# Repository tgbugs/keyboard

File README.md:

# kicad libs and mods needed
https://github.com/tmk/kicad_lib_tmk.git
https://github.com/tmk/keyboard_parts.pretty
https://github.com/stormbard/Keyboard.pretty.git
https://github.com/XenGi/kicad_teensy.git
# use this guide
https://github.com/ruiqimao/keyboard-pcb-guide
# keyboard layout editor
https://github.com/swill/kb_builder
http://www.keyboard-layout-editor.com
# teensy setup on gentoo
Need dev-embedded/teensyduino and dev-embedded/teensy_loader_cli, working ebuilds in https://github.com/tgbugs/tgbugs-overlay.
# freerout is basically a necisity use this repo
https://github.com/nick-less/freerouting
Some setup needed to get maven to play nice. Just read the errors.
# gerbv
Before shipping out the gerber files do a once over in something other than kicad. `emerge gerbv`

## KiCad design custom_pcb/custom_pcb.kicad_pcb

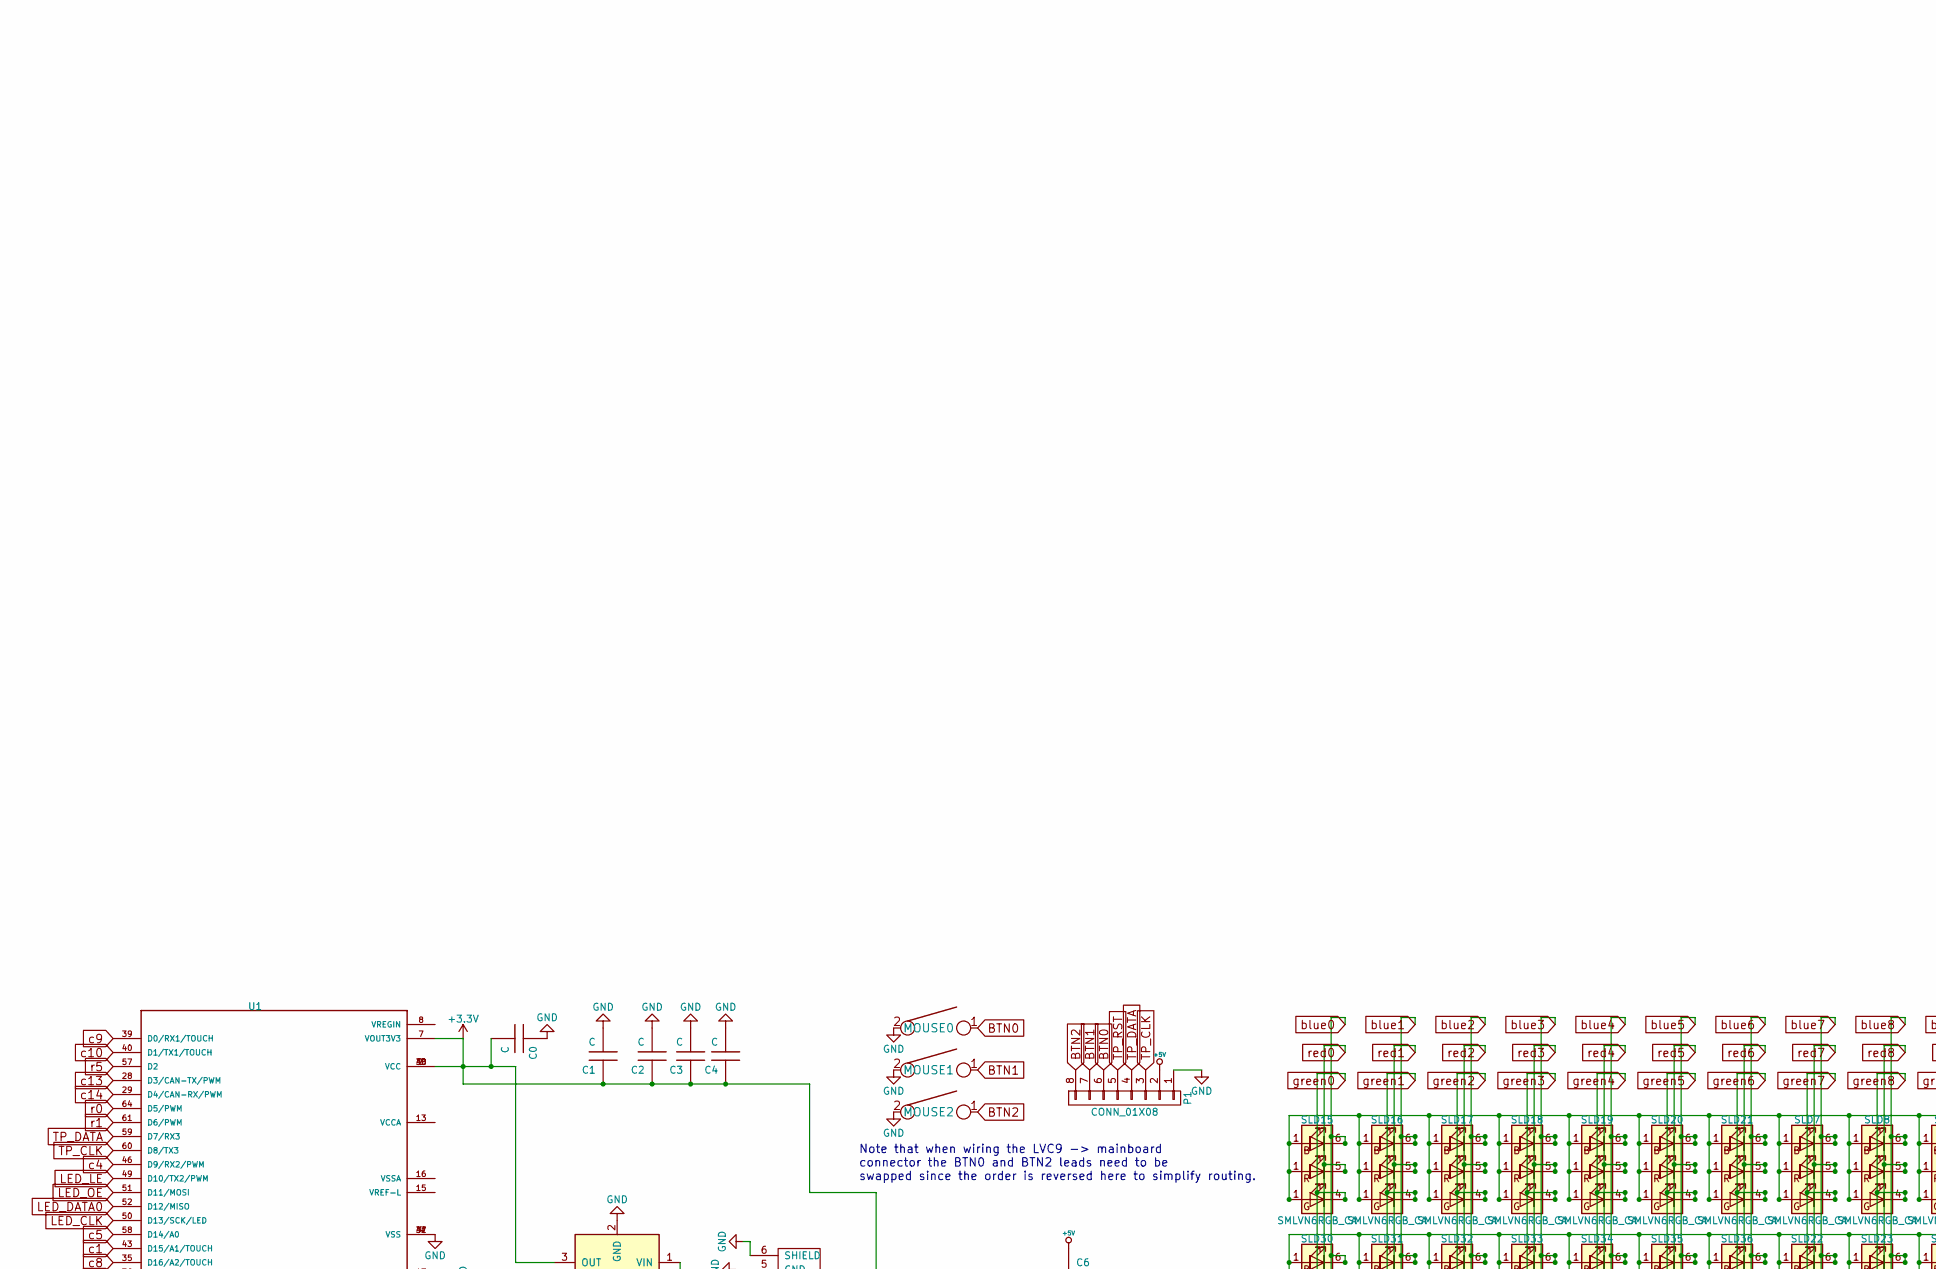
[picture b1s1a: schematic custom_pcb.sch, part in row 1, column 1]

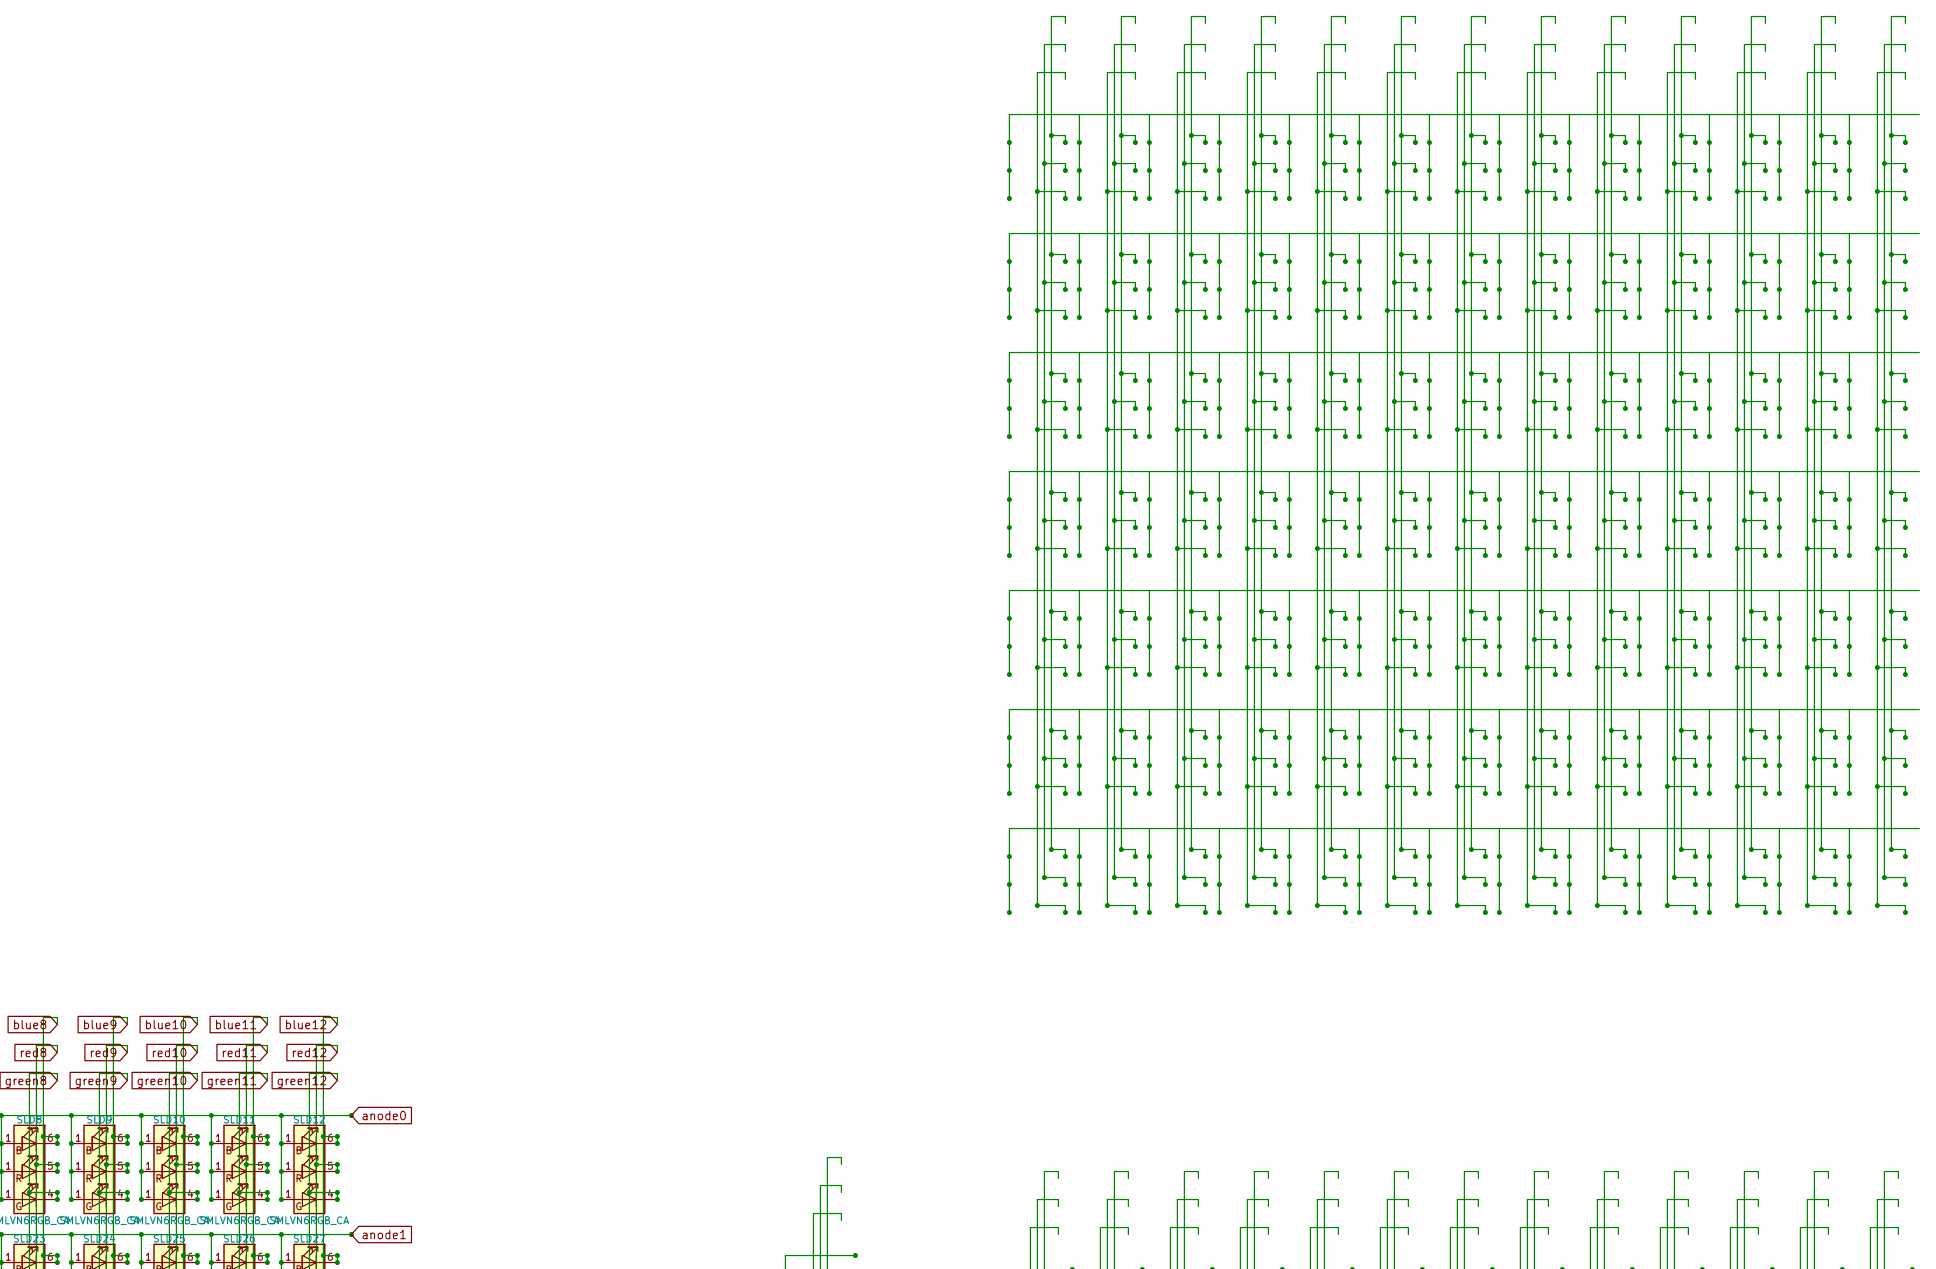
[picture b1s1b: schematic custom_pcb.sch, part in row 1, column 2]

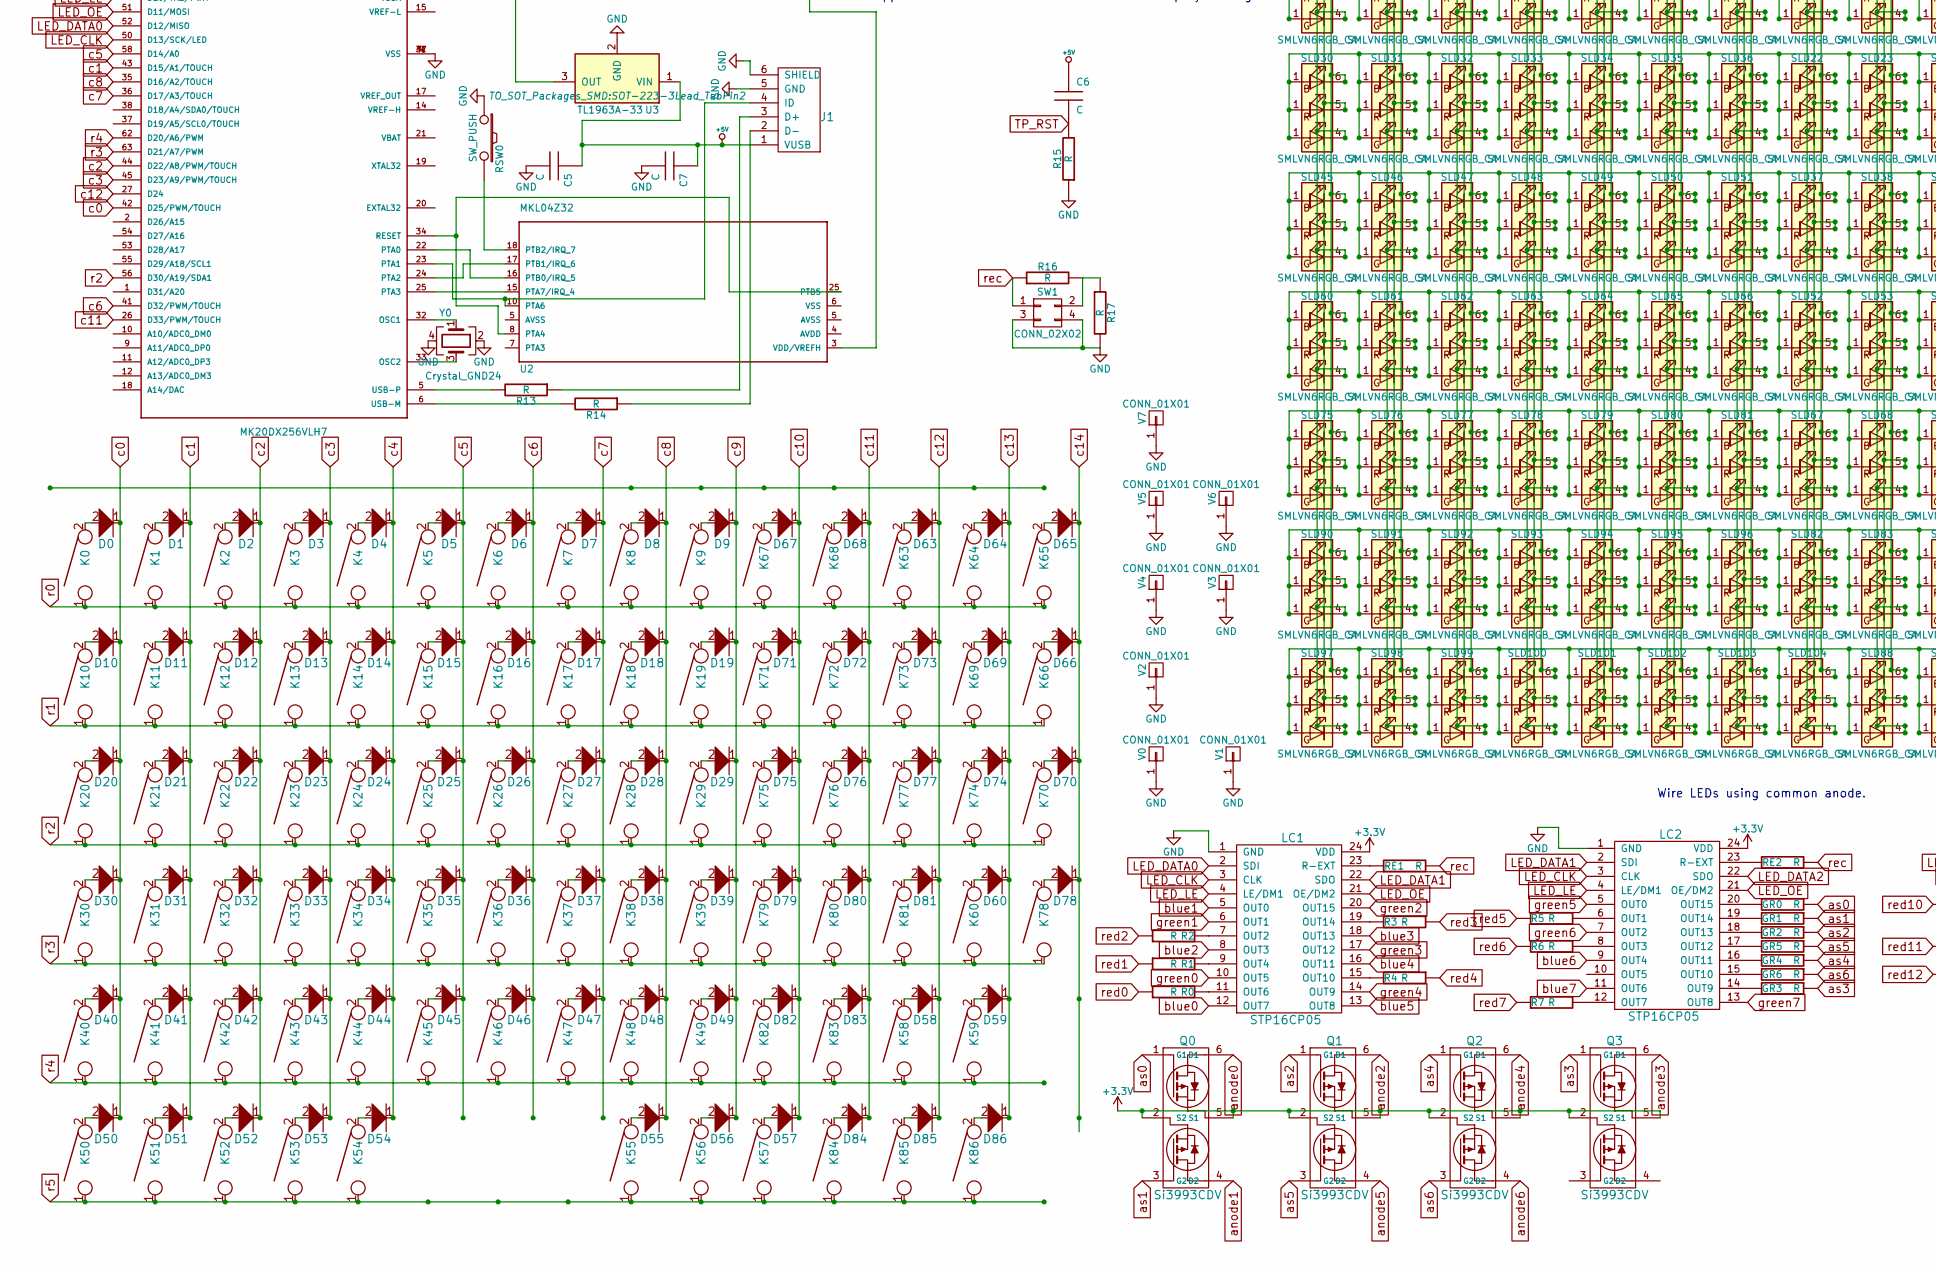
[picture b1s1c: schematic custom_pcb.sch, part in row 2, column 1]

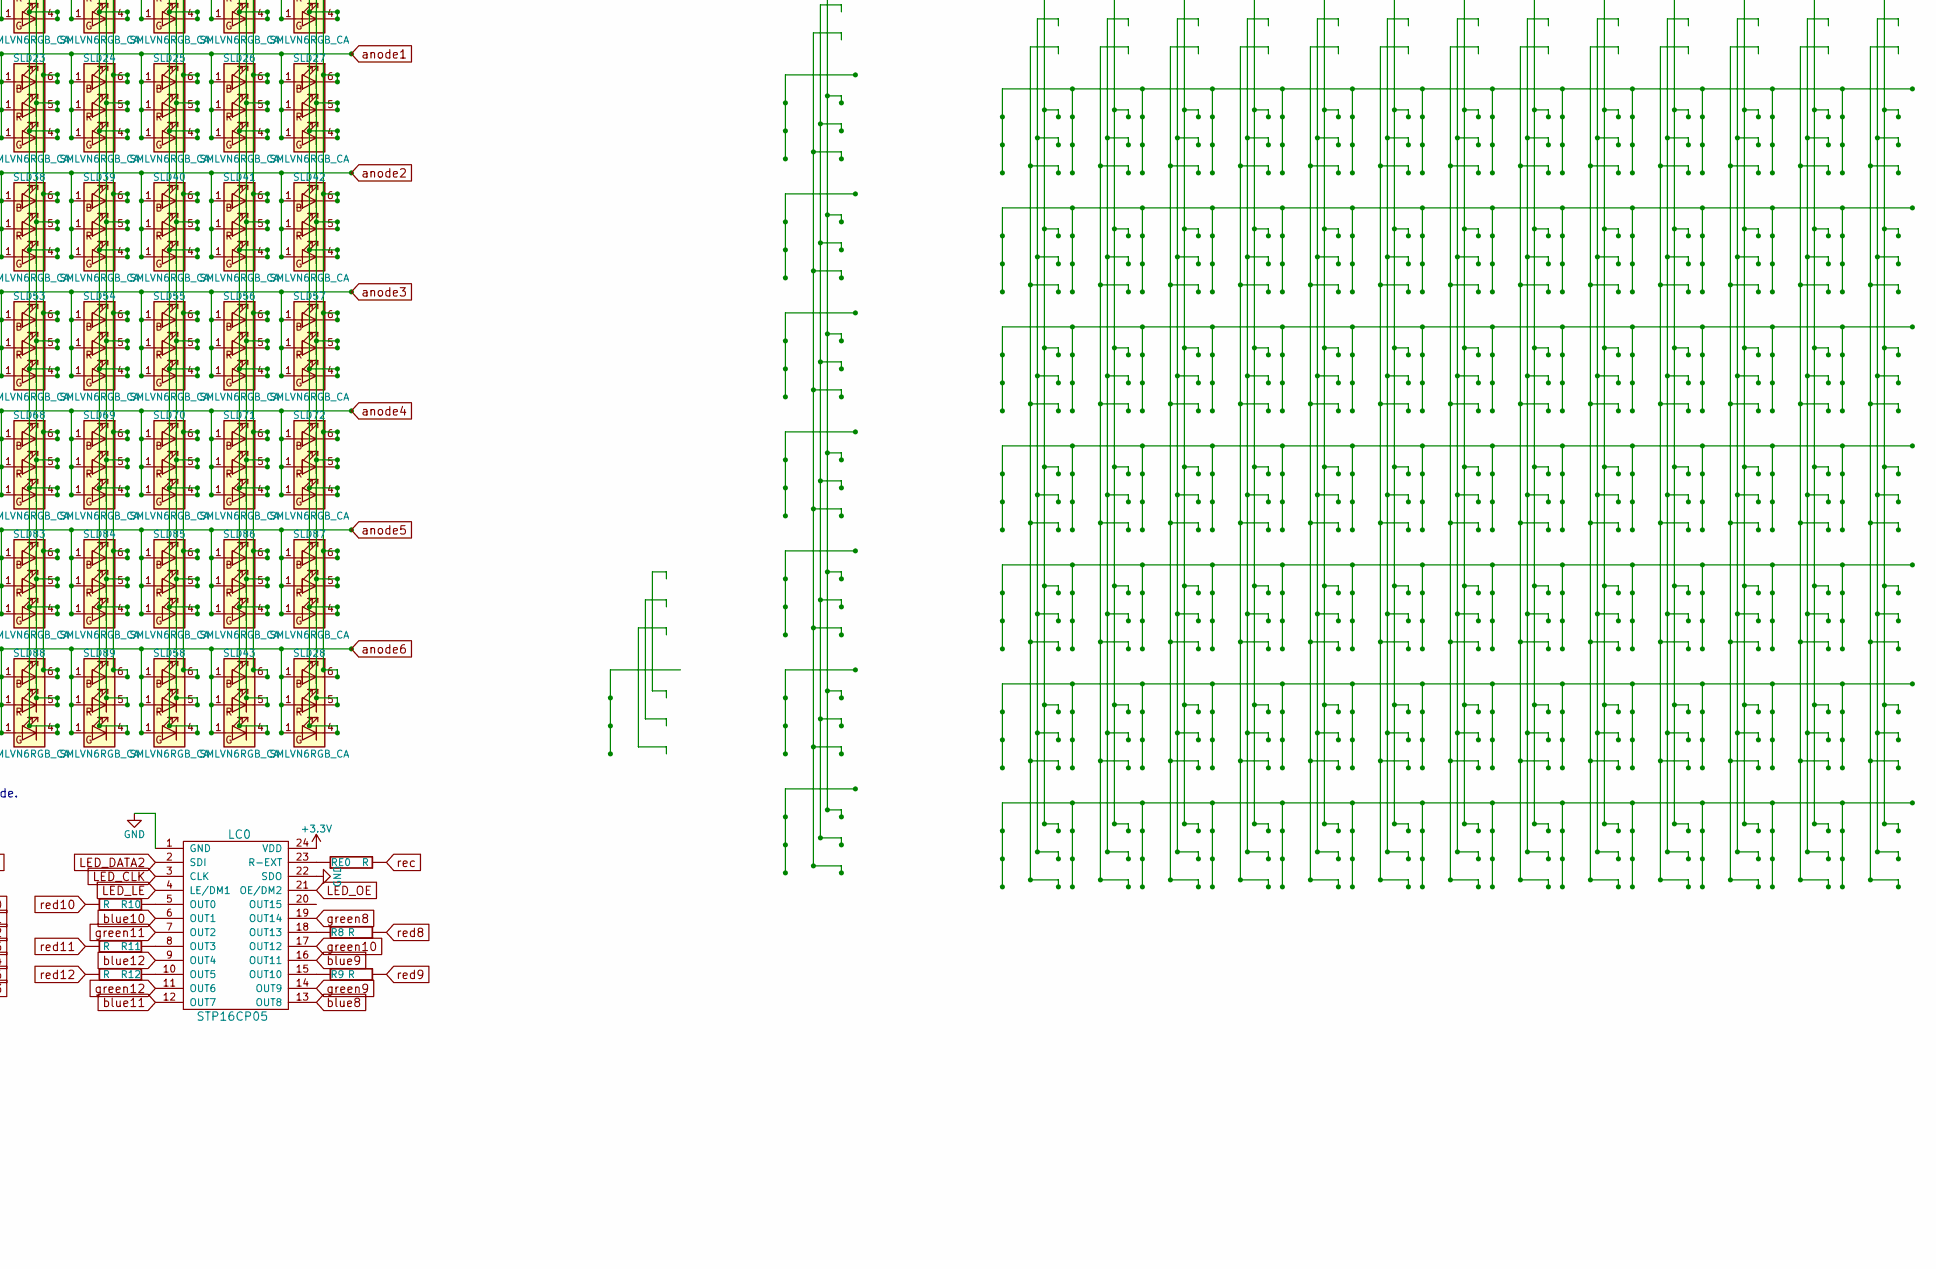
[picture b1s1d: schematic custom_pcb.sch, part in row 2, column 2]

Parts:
C0, C1, C2, C3, C4, C5, C6, C7: C; C_0603_HandSoldering
D0, D1, D2, D3, D4, D5, D6, D7, D8, D9, D10, D11, D12, D13, D14, D15, D16, D17, D18, D19, D20, D21, D22, D23, D24, D25, D26, D27, D28, D29, D30, D31, D32, D33, D34, D35, D36, D37, D38, D39, D40, D41, D42, D43, D44, D45, D46, D47, D48, D49, D50, D51, D52, D53, D54, D55, D56, D57, D58, D59, D60, D63, D64, D65, D66, D67, D68, D69, D70, D71, D72, D73, D74, D75, D76, D77, D78, D79, D80, D81, D82, D83, D84, D85, D86: D; D_SOD-123
GR0, GR1, GR2, GR3, GR4, GR5, GR6: R; R_0402_NoSilk
J1: USB_mini_micro_B; USB_miniB_hirose_5S8
K0, K64: KEYSW; CHERRY_PLATE_200V
K1, K2, K3, K4, K5, K6, K7, K8, K9, K63, K67, K68: KEYSW; CHERRY_PLATE_91.6H
K10, K11, K12, K13, K14, K15, K16, K17, K18, K19, K21, K22, K23, K24, K25, K26, K27, K28, K29, K31, K32, K33, K34, K35, K36, K37, K38, K39, K41, K42, K43, K44, K45, K46, K47, K48, K49, K50, K52, K53, K57, K58, K59, K60, K65, K66, K69, K70, K71, K72, K73, K75, K76, K77, K79, K80, K82, K84, K85, K86: KEYSW; CHERRY_PLATE_100H
K20, K56, K78: KEYSW; CHERRY_PLATE_150H
K30: KEYSW; CHERRY_PLATE_175H
K40, K81: KEYSW; CHERRY_PLATE_225H
K51, K55: KEYSW; CHERRY_PLATE_125H
K54: KEYSW; CHERRY_PLATE_5000H
K74: KEYSW; CHERRY_PLATE_200H
K83: KEYSW; CHERRY_PLATE_175_275H
LC0, LC1, LC2: STP16CP05; TSSOP-24_4.4x7.8mm_Pitch0.65mm
MOUSE0, MOUSE2: KEYSW; CHERRY_PLATE_150H
MOUSE1: KEYSW; CHERRY_PLATE_100H
P1: CONN_01X08; Molex_PicoBlade_53261-0871_08x1.25mm_Angled
Q0, Q1, Q2, Q3: Si3993CDV; SOT-23-6_Handsoldering
R0, R1, R2, R3, R4, R5, R6, R7, R8, R9, R10, R11, R12, R13, R14, R15, R16, R17: R; R_0603_HandSoldering
RE0, RE1, RE2: R; R_0603_HandSoldering
RSW0: SW_PUSH; SW_SPST_B3U-1000P
SLD7, SLD8, SLD9, SLD10, SLD11, SLD12, SLD15, SLD16, SLD17, SLD18, SLD19, SLD20, SLD21, SLD22, SLD23, SLD24, SLD25, SLD26, SLD27, SLD28, SLD30, SLD31, SLD32, SLD33, SLD34, SLD35, SLD36, SLD37, SLD38, SLD39, SLD40, SLD41, SLD42, SLD43, SLD45, SLD46, SLD47, SLD48, SLD49, SLD50, SLD51, SLD52, SLD53, SLD54, SLD55, SLD56, SLD57, SLD58, SLD60, SLD61, SLD62, SLD63, SLD64, SLD65, SLD66, SLD67, SLD68, SLD69, SLD70, SLD71, SLD72, SLD75, SLD76, SLD77, SLD78, SLD79, SLD80, SLD81, SLD82, SLD83, SLD84, SLD85, SLD86, SLD87, SLD88, SLD89, SLD90, SLD91, SLD92, SLD93, SLD94, SLD95, SLD96, SLD97, SLD98, SLD99, SLD100, SLD101, SLD102, SLD103, SLD104: SMLVN6RGB_CA
SW1: CONN_02X02; CVS-02TB
U1: MK20DX256VLH7; QFP50P1200X1200X160-64N
U2: MKL04Z32; QFP50P900X900X160-48N
U3: TL1963A-33; SOT-223-3Lead_TabPin2
V0, V1, V2, V6: CONN_01X01; VIA100
V3, V4, V5, V7: CONN_01X01; VIA127
Y0: Crystal_GND24; Crystal_SMD_3225-4pin_3.2x2.5mm_HandSoldering

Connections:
+3V3: C0.2, C1.1, C2.1, C3.1, C4.1, LC0.24 (VDD), LC1.24 (VDD), LC2.24 (VDD), Q0.2 (S2), Q0.5 (S1), Q1.2 (S2), Q1.5 (S1), Q2.2 (S2), Q2.5 (S1), Q3.2 (S2), Q3.5 (S1), U1.3 (VCC), U1.7 (VOUT3V3), U1.30 (VCC), U1.48 (VCC), U2.3 (VDD/VREFH), U3.3 (OUT)
+5V: C5.1, C6.1, C7.1, J1.1 (VUSB), P1.2, U3.1 (VIN)
BTN0: MOUSE0.1, P1.6
BTN1: MOUSE1.1, P1.7
BTN2: MOUSE2.1, P1.8
GND: C0.1, C1.2, C2.2, C3.2, C4.2, C5.2, C7.2, J1.5 (GND), J1.6 (SHIELD), LC0.1 (GND), LC0.22 (SDO), LC1.1 (GND), LC2.1 (GND), MOUSE0.2, MOUSE1.2, MOUSE2.2, P1.1, R15.1, R17.2, RSW0.1, SW1.3, SW1.4, U1.4 (VSS), U1.31 (VSS), U1.47 (VSS), U3.2 (GND), V0.1, V1.1, V2.1, V3.1, V4.1, V5.1, V6.1, V7.1, Y0.2, Y0.4
LED_CLK: LC0.3 (CLK), LC1.3 (CLK), LC2.3 (CLK), U1.50 (D13/SCK/LED)
LED_DATA0: LC1.2 (SDI), U1.52 (D12/MISO)
LED_DATA1: LC1.22 (SDO), LC2.2 (SDI)
LED_DATA2: LC0.2 (SDI), LC2.22 (SDO)
LED_LE: LC0.4 (LE/DM1), LC1.4 (LE/DM1), LC2.4 (LE/DM1), U1.49 (D10/TX2/PWM)
LED_OE: LC0.21 (OE/DM2), LC1.21 (OE/DM2), LC2.21 (OE/DM2), U1.51 (D11/MOSI)
unnamed: D0.2, K0.2
unnamed: D1.2, K1.2
unnamed: D2.2, K2.2
unnamed: D3.2, K3.2
unnamed: D4.2, K4.2
unnamed: D5.2, K5.2
unnamed: D6.2, K6.2
unnamed: D7.2, K7.2
unnamed: D8.2, K8.2
unnamed: D9.2, K9.2
unnamed: D10.2, K10.2
unnamed: D11.2, K11.2
unnamed: D12.2, K12.2
unnamed: D13.2, K13.2
unnamed: D14.2, K14.2
unnamed: D15.2, K15.2
unnamed: D16.2, K16.2
unnamed: D17.2, K17.2
unnamed: D18.2, K18.2
unnamed: D19.2, K19.2
unnamed: D20.2, K20.2
unnamed: D21.2, K21.2
unnamed: D22.2, K22.2
unnamed: D23.2, K23.2
unnamed: D24.2, K24.2
unnamed: D25.2, K25.2
unnamed: D26.2, K26.2
unnamed: D27.2, K27.2
unnamed: D28.2, K28.2
unnamed: D29.2, K29.2
unnamed: D30.2, K30.2
unnamed: D31.2, K31.2
unnamed: D32.2, K32.2
unnamed: D33.2, K33.2
unnamed: D34.2, K34.2
unnamed: D35.2, K35.2
unnamed: D36.2, K36.2
unnamed: D37.2, K37.2
unnamed: D38.2, K38.2
unnamed: D39.2, K39.2
unnamed: D40.2, K40.2
unnamed: D41.2, K41.2
unnamed: D42.2, K42.2
unnamed: D43.2, K43.2
unnamed: D44.2, K44.2
unnamed: D45.2, K45.2
unnamed: D46.2, K46.2
unnamed: D47.2, K47.2
unnamed: D48.2, K48.2
unnamed: D49.2, K49.2
unnamed: D50.2, K50.2
unnamed: D51.2, K51.2
unnamed: D52.2, K52.2
unnamed: D53.2, K53.2
unnamed: D54.2, K54.2
unnamed: D55.2, K55.2
unnamed: D56.2, K56.2
unnamed: D57.2, K57.2
unnamed: D58.2, K58.2
unnamed: D59.2, K59.2
unnamed: D60.2, K60.2
unnamed: D63.2, K63.2
unnamed: D64.2, K64.2
unnamed: D65.2, K65.2
unnamed: D66.2, K66.2
unnamed: D67.2, K67.2
unnamed: D68.2, K68.2
unnamed: D69.2, K69.2
unnamed: D70.2, K70.2
unnamed: D71.2, K71.2
unnamed: D72.2, K72.2
unnamed: D73.2, K73.2
unnamed: D74.2, K74.2
unnamed: D75.2, K75.2
unnamed: D76.2, K76.2
unnamed: D77.2, K77.2
unnamed: D78.2, K78.2
unnamed: D79.2, K79.2
unnamed: D80.2, K80.2
unnamed: D81.2, K81.2
unnamed: D82.2, K82.2
unnamed: D83.2, K83.2
unnamed: D84.2, K84.2
unnamed: D85.2, K85.2
unnamed: D86.2, K86.2
unnamed: GR0.2, LC2.20 (OUT15)
unnamed: GR1.2, LC2.19 (OUT14)
unnamed: GR2.2, LC2.18 (OUT13)
unnamed: GR3.2, LC2.14 (OUT9)
unnamed: GR4.2, LC2.16 (OUT11)
unnamed: GR5.2, LC2.17 (OUT12)
unnamed: GR6.2, LC2.15 (OUT10)
unnamed: J1.2 (D-), R14.1
unnamed: J1.3 (D+), R13.1
unnamed: J1.4 (ID), U1.23 (PTA1), U2.10 (PTA6)
unnamed: LC0.5 (OUT0), R10.1
unnamed: LC0.8 (OUT3), R11.1
unnamed: LC0.10 (OUT5), R12.1
unnamed: LC0.15 (OUT10), R9.1
unnamed: LC0.18 (OUT13), R8.1
unnamed: LC0.23 (R-EXT), RE0.1
unnamed: LC1.7 (OUT2), R2.2
unnamed: LC1.9 (OUT4), R1.2
unnamed: LC1.11 (OUT6), R0.2
unnamed: LC1.15 (OUT10), R4.2
unnamed: LC1.19 (OUT14), R3.2
unnamed: LC1.23 (R-EXT), RE1.1
unnamed: LC2.6 (OUT1), R5.2
unnamed: LC2.8 (OUT3), R6.2
unnamed: LC2.12 (OUT7), R7.2
unnamed: LC2.23 (R-EXT), RE2.1
unnamed: R13.2, U1.5 (USB-P)
unnamed: R14.2, U1.6 (USB-M)
unnamed: R16.2, R17.1, SW1.2
unnamed: RSW0.2, U2.18 (PTB2/IRQ_7)
unnamed: U1.22 (PTA0), U2.16 (PTB0/IRQ_5)
unnamed: U1.24 (PTA2), U2.17 (PTB1/IRQ_6)
unnamed: U1.25 (PTA3), U2.15 (PTA7/IRQ_4)
unnamed: U1.32 (OSC1), Y0.1
unnamed: U1.33 (OSC2), Y0.3
unnamed: U1.34 (RESET), U2.8 (PTA4), U2.25 (PTB5)
TP_CLK: P1.3, U1.60 (D8/TX3)
TP_DATA: P1.4, U1.59 (D7/RX3)
TP_RST: C6.2, P1.5, R15.2
anode0: Q0.6 (D1), SLD7.1 (BK), SLD8.1 (BK), SLD9.1 (BK), SLD10.1 (BK), SLD11.1 (BK), SLD12.1 (BK), SLD15.1 (BK), SLD16.1 (BK), SLD17.1 (BK), SLD18.1 (BK), SLD19.1 (BK), SLD20.1 (BK), SLD21.1 (BK)
anode1: Q0.4 (D2), SLD22.1 (BK), SLD23.1 (BK), SLD24.1 (BK), SLD25.1 (BK), SLD26.1 (BK), SLD27.1 (BK), SLD30.1 (BK), SLD31.1 (BK), SLD32.1 (BK), SLD33.1 (BK), SLD34.1 (BK), SLD35.1 (BK), SLD36.1 (BK)
anode2: Q1.6 (D1), SLD37.1 (BK), SLD38.1 (BK), SLD39.1 (BK), SLD40.1 (BK), SLD41.1 (BK), SLD42.1 (BK), SLD45.1 (BK), SLD46.1 (BK), SLD47.1 (BK), SLD48.1 (BK), SLD49.1 (BK), SLD50.1 (BK), SLD51.1 (BK)
anode3: Q3.6 (D1), SLD52.1 (BK), SLD53.1 (BK), SLD54.1 (BK), SLD55.1 (BK), SLD56.1 (BK), SLD57.1 (BK), SLD60.1 (BK), SLD61.1 (BK), SLD62.1 (BK), SLD63.1 (BK), SLD64.1 (BK), SLD65.1 (BK), SLD66.1 (BK)
anode4: Q2.6 (D1), SLD67.1 (BK), SLD68.1 (BK), SLD69.1 (BK), SLD70.1 (BK), SLD71.1 (BK), SLD72.1 (BK), SLD75.1 (BK), SLD76.1 (BK), SLD77.1 (BK), SLD78.1 (BK), SLD79.1 (BK), SLD80.1 (BK), SLD81.1 (BK)
anode5: Q1.4 (D2), SLD82.1 (BK), SLD83.1 (BK), SLD84.1 (BK), SLD85.1 (BK), SLD86.1 (BK), SLD87.1 (BK), SLD90.1 (BK), SLD91.1 (BK), SLD92.1 (BK), SLD93.1 (BK), SLD94.1 (BK), SLD95.1 (BK), SLD96.1 (BK)
anode6: Q2.4 (D2), SLD28.1 (BK), SLD43.1 (BK), SLD58.1 (BK), SLD88.1 (BK), SLD89.1 (BK), SLD97.1 (BK), SLD98.1 (BK), SLD99.1 (BK), SLD100.1 (BK), SLD101.1 (BK), SLD102.1 (BK), SLD103.1 (BK), SLD104.1 (BK)
as0: GR0.1, Q0.1 (G1)
as1: GR1.1, Q0.3 (G2)
as2: GR2.1, Q1.1 (G1)
as3: GR3.1, Q3.1 (G1)
as4: GR4.1, Q2.1 (G1)
as5: GR5.1, Q1.3 (G2)
as6: GR6.1, Q2.3 (G2)
blue0: LC1.12 (OUT7), SLD15.6 (RA), SLD30.6 (RA), SLD45.6 (RA), SLD60.6 (RA), SLD75.6 (RA), SLD90.6 (RA), SLD97.6 (RA)
blue1: LC1.5 (OUT0), SLD16.6 (RA), SLD31.6 (RA), SLD46.6 (RA), SLD61.6 (RA), SLD76.6 (RA), SLD91.6 (RA), SLD98.6 (RA)
blue2: LC1.8 (OUT3), SLD17.6 (RA), SLD32.6 (RA), SLD47.6 (RA), SLD62.6 (RA), SLD77.6 (RA), SLD92.6 (RA), SLD99.6 (RA)
blue3: LC1.18 (OUT13), SLD18.6 (RA), SLD33.6 (RA), SLD48.6 (RA), SLD63.6 (RA), SLD78.6 (RA), SLD93.6 (RA), SLD100.6 (RA)
blue4: LC1.16 (OUT11), SLD19.6 (RA), SLD34.6 (RA), SLD49.6 (RA), SLD64.6 (RA), SLD79.6 (RA), SLD94.6 (RA), SLD101.6 (RA)
blue5: LC1.13 (OUT8), SLD20.6 (RA), SLD35.6 (RA), SLD50.6 (RA), SLD65.6 (RA), SLD80.6 (RA), SLD95.6 (RA), SLD102.6 (RA)
blue6: LC2.9 (OUT4), SLD21.6 (RA), SLD36.6 (RA), SLD51.6 (RA), SLD66.6 (RA), SLD81.6 (RA), SLD96.6 (RA), SLD103.6 (RA)
blue7: LC2.11 (OUT6), SLD7.6 (RA), SLD22.6 (RA), SLD37.6 (RA), SLD52.6 (RA), SLD67.6 (RA), SLD82.6 (RA), SLD104.6 (RA)
blue8: LC0.13 (OUT8), SLD8.6 (RA), SLD23.6 (RA), SLD38.6 (RA), SLD53.6 (RA), SLD68.6 (RA), SLD83.6 (RA), SLD88.6 (RA)
blue9: LC0.16 (OUT11), SLD9.6 (RA), SLD24.6 (RA), SLD39.6 (RA), SLD54.6 (RA), SLD69.6 (RA), SLD84.6 (RA), SLD89.6 (RA)
blue10: LC0.6 (OUT1), SLD10.6 (RA), SLD25.6 (RA), SLD40.6 (RA), SLD55.6 (RA), SLD58.6 (RA), SLD70.6 (RA), SLD85.6 (RA)
blue11: LC0.12 (OUT7), SLD11.6 (RA), SLD26.6 (RA), SLD41.6 (RA), SLD43.6 (RA), SLD56.6 (RA), SLD71.6 (RA), SLD86.6 (RA)
blue12: LC0.9 (OUT4), SLD12.6 (RA), SLD27.6 (RA), SLD28.6 (RA), SLD42.6 (RA), SLD57.6 (RA), SLD72.6 (RA), SLD87.6 (RA)
c0: D0.1, D10.1, D20.1, D30.1, D40.1, D50.1, U1.42 (D25/PWM/TOUCH)
c1: D1.1, D11.1, D21.1, D31.1, D41.1, D51.1, U1.43 (D15/A1/TOUCH)
c2: D2.1, D12.1, D22.1, D32.1, D42.1, D52.1, U1.44 (D22/A8/PWM/TOUCH)
c3: D3.1, D13.1, D23.1, D33.1, D43.1, D53.1, U1.45 (D23/A9/PWM/TOUCH)
c4: D4.1, D14.1, D24.1, D34.1, D44.1, D54.1, U1.46 (D9/RX2/PWM)
c5: D5.1, D15.1, D25.1, D35.1, D45.1, U1.58 (D14/A0)
c6: D6.1, D16.1, D26.1, D36.1, D46.1, U1.41 (D32/PWM/TOUCH)
c7: D7.1, D17.1, D27.1, D37.1, D47.1, U1.36 (D17/A3/TOUCH)
c8: D8.1, D18.1, D28.1, D38.1, D48.1, D55.1, U1.35 (D16/A2/TOUCH)
c9: D9.1, D19.1, D29.1, D39.1, D49.1, D56.1, U1.39 (D0/RX1/TOUCH)
c10: D57.1, D67.1, D71.1, D75.1, D79.1, D82.1, U1.40 (D1/TX1/TOUCH)
c11: D68.1, D72.1, D76.1, D80.1, D83.1, D84.1, U1.26 (D33/PWM/TOUCH)
c12: D58.1, D63.1, D73.1, D77.1, D81.1, D85.1, U1.27 (D24)
c13: D59.1, D60.1, D64.1, D69.1, D74.1, D86.1, U1.28 (D3/CAN-TX/PWM)
c14: D65.1, D66.1, D70.1, D78.1, U1.29 (D4/CAN-RX/PWM)
green0: LC1.10 (OUT5), SLD15.4 (BA), SLD30.4 (BA), SLD45.4 (BA), SLD60.4 (BA), SLD75.4 (BA), SLD90.4 (BA), SLD97.4 (BA)
green1: LC1.6 (OUT1), SLD16.4 (BA), SLD31.4 (BA), SLD46.4 (BA), SLD61.4 (BA), SLD76.4 (BA), SLD91.4 (BA), SLD98.4 (BA)
green2: LC1.20 (OUT15), SLD17.4 (BA), SLD32.4 (BA), SLD47.4 (BA), SLD62.4 (BA), SLD77.4 (BA), SLD92.4 (BA), SLD99.4 (BA)
green3: LC1.17 (OUT12), SLD18.4 (BA), SLD33.4 (BA), SLD48.4 (BA), SLD63.4 (BA), SLD78.4 (BA), SLD93.4 (BA), SLD100.4 (BA)
green4: LC1.14 (OUT9), SLD19.4 (BA), SLD34.4 (BA), SLD49.4 (BA), SLD64.4 (BA), SLD79.4 (BA), SLD94.4 (BA), SLD101.4 (BA)
green5: LC2.5 (OUT0), SLD20.4 (BA), SLD35.4 (BA), SLD50.4 (BA), SLD65.4 (BA), SLD80.4 (BA), SLD95.4 (BA), SLD102.4 (BA)
green6: LC2.7 (OUT2), SLD21.4 (BA), SLD36.4 (BA), SLD51.4 (BA), SLD66.4 (BA), SLD81.4 (BA), SLD96.4 (BA), SLD103.4 (BA)
green7: LC2.13 (OUT8), SLD7.4 (BA), SLD22.4 (BA), SLD37.4 (BA), SLD52.4 (BA), SLD67.4 (BA), SLD82.4 (BA), SLD104.4 (BA)
green8: LC0.19 (OUT14), SLD8.4 (BA), SLD23.4 (BA), SLD38.4 (BA), SLD53.4 (BA), SLD68.4 (BA), SLD83.4 (BA), SLD88.4 (BA)
green9: LC0.14 (OUT9), SLD9.4 (BA), SLD24.4 (BA), SLD39.4 (BA), SLD54.4 (BA), SLD69.4 (BA), SLD84.4 (BA), SLD89.4 (BA)
green10: LC0.17 (OUT12), SLD10.4 (BA), SLD25.4 (BA), SLD40.4 (BA), SLD55.4 (BA), SLD58.4 (BA), SLD70.4 (BA), SLD85.4 (BA)
green11: LC0.7 (OUT2), SLD11.4 (BA), SLD26.4 (BA), SLD41.4 (BA), SLD43.4 (BA), SLD56.4 (BA), SLD71.4 (BA), SLD86.4 (BA)
green12: LC0.11 (OUT6), SLD12.4 (BA), SLD27.4 (BA), SLD28.4 (BA), SLD42.4 (BA), SLD57.4 (BA), SLD72.4 (BA), SLD87.4 (BA)
r0: K0.1, K1.1, K2.1, K3.1, K4.1, K5.1, K6.1, K7.1, K8.1, K9.1, K63.1, K64.1, K65.1, K67.1, K68.1, U1.64 (D5/PWM)
r1: K10.1, K11.1, K12.1, K13.1, K14.1, K15.1, K16.1, K17.1, K18.1, K19.1, K66.1, K69.1, K71.1, K72.1, K73.1, U1.61 (D6/PWM)
r2: K20.1, K21.1, K22.1, K23.1, K24.1, K25.1, K26.1, K27.1, K28.1, K29.1, K70.1, K74.1, K75.1, K76.1, K77.1, U1.56 (D30/A19/SDA1)
r3: K30.1, K31.1, K32.1, K33.1, K34.1, K35.1, K36.1, K37.1, K38.1, K39.1, K60.1, K78.1, K79.1, K80.1, K81.1, U1.63 (D21/A7/PWM)
r4: K40.1, K41.1, K42.1, K43.1, K44.1, K45.1, K46.1, K47.1, K48.1, K49.1, K58.1, K59.1, K82.1, K83.1, U1.62 (D20/A6/PWM)
r5: K50.1, K51.1, K52.1, K53.1, K54.1, K55.1, K56.1, K57.1, K84.1, K85.1, K86.1, U1.57 (D2)
rec: R16.1, RE0.2, RE1.2, RE2.2, SW1.1
red0: R0.1, SLD15.5 (GA), SLD30.5 (GA), SLD45.5 (GA), SLD60.5 (GA), SLD75.5 (GA), SLD90.5 (GA), SLD97.5 (GA)
red1: R1.1, SLD16.5 (GA), SLD31.5 (GA), SLD46.5 (GA), SLD61.5 (GA), SLD76.5 (GA), SLD91.5 (GA), SLD98.5 (GA)
red2: R2.1, SLD17.5 (GA), SLD32.5 (GA), SLD47.5 (GA), SLD62.5 (GA), SLD77.5 (GA), SLD92.5 (GA), SLD99.5 (GA)
red3: R3.1, SLD18.5 (GA), SLD33.5 (GA), SLD48.5 (GA), SLD63.5 (GA), SLD78.5 (GA), SLD93.5 (GA), SLD100.5 (GA)
red4: R4.1, SLD19.5 (GA), SLD34.5 (GA), SLD49.5 (GA), SLD64.5 (GA), SLD79.5 (GA), SLD94.5 (GA), SLD101.5 (GA)
red5: R5.1, SLD20.5 (GA), SLD35.5 (GA), SLD50.5 (GA), SLD65.5 (GA), SLD80.5 (GA), SLD95.5 (GA), SLD102.5 (GA)
red6: R6.1, SLD21.5 (GA), SLD36.5 (GA), SLD51.5 (GA), SLD66.5 (GA), SLD81.5 (GA), SLD96.5 (GA), SLD103.5 (GA)
red7: R7.1, SLD7.5 (GA), SLD22.5 (GA), SLD37.5 (GA), SLD52.5 (GA), SLD67.5 (GA), SLD82.5 (GA), SLD104.5 (GA)
red8: R8.2, SLD8.5 (GA), SLD23.5 (GA), SLD38.5 (GA), SLD53.5 (GA), SLD68.5 (GA), SLD83.5 (GA), SLD88.5 (GA)
red9: R9.2, SLD9.5 (GA), SLD24.5 (GA), SLD39.5 (GA), SLD54.5 (GA), SLD69.5 (GA), SLD84.5 (GA), SLD89.5 (GA)
red10: R10.2, SLD10.5 (GA), SLD25.5 (GA), SLD40.5 (GA), SLD55.5 (GA), SLD58.5 (GA), SLD70.5 (GA), SLD85.5 (GA)
red11: R11.2, SLD11.5 (GA), SLD26.5 (GA), SLD41.5 (GA), SLD43.5 (GA), SLD56.5 (GA), SLD71.5 (GA), SLD86.5 (GA)
red12: R12.2, SLD12.5 (GA), SLD27.5 (GA), SLD28.5 (GA), SLD42.5 (GA), SLD57.5 (GA), SLD72.5 (GA), SLD87.5 (GA)

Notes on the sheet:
Note that when wiring the LVC9 -> mainboard connector the BTN0 and BTN2 leads need to be swapped since the order is reversed here to simplify routing.
Wire LEDs using common anode.

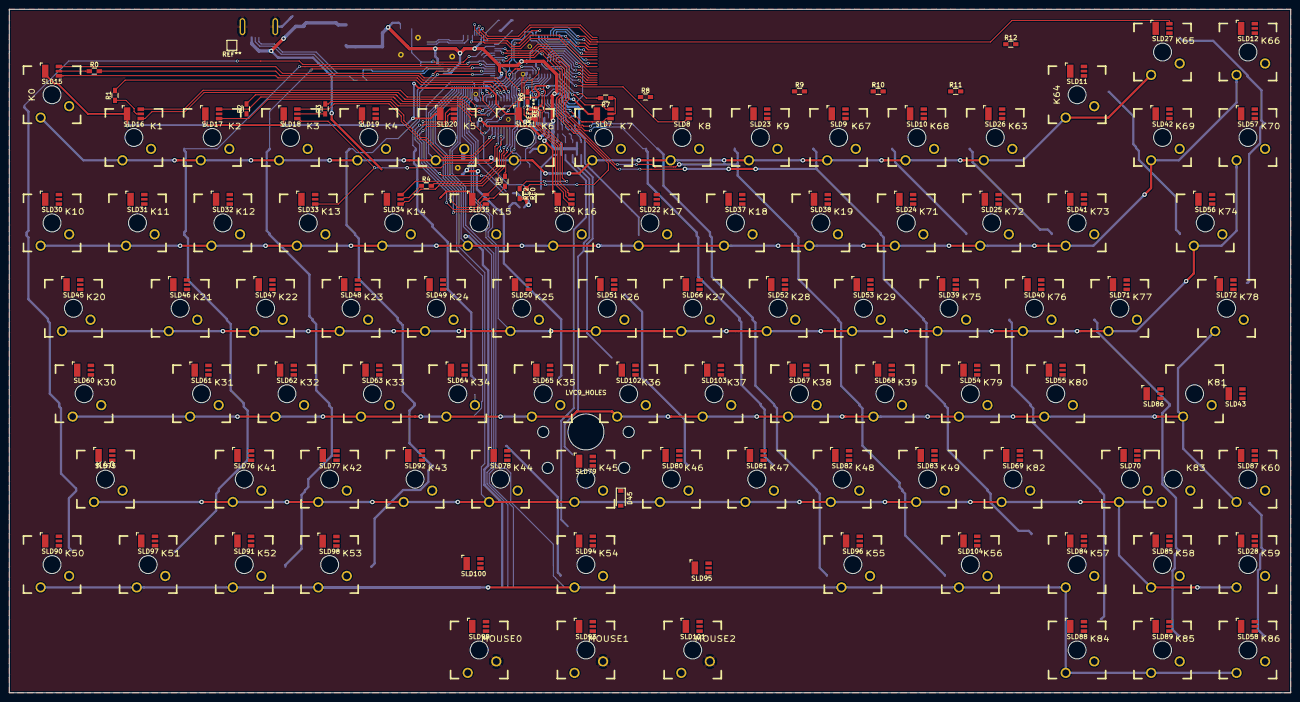
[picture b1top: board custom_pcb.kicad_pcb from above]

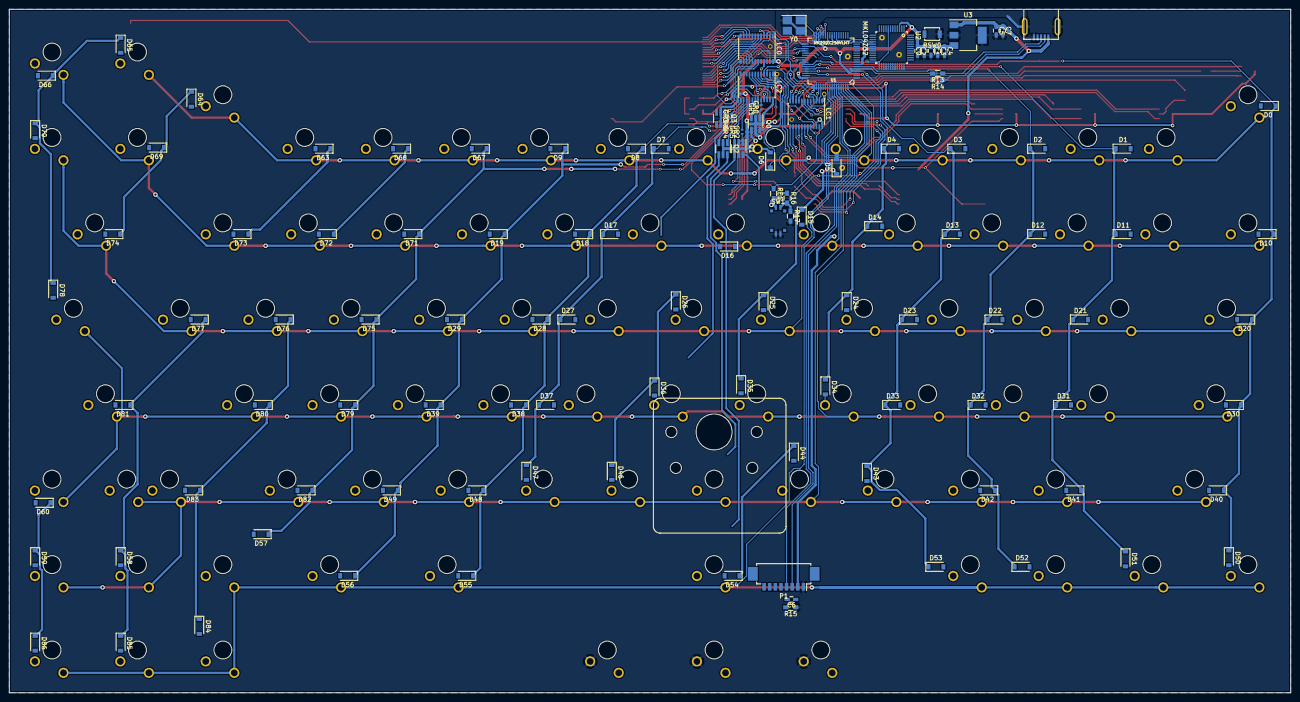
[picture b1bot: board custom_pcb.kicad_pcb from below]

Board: 2 copper layers, 285.0 x 152.0 mm, 324 parts (120 on the bottom side), 211 nets.

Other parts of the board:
LVC9_HOLES: LVC9 Attach; LVC9_HOLES
